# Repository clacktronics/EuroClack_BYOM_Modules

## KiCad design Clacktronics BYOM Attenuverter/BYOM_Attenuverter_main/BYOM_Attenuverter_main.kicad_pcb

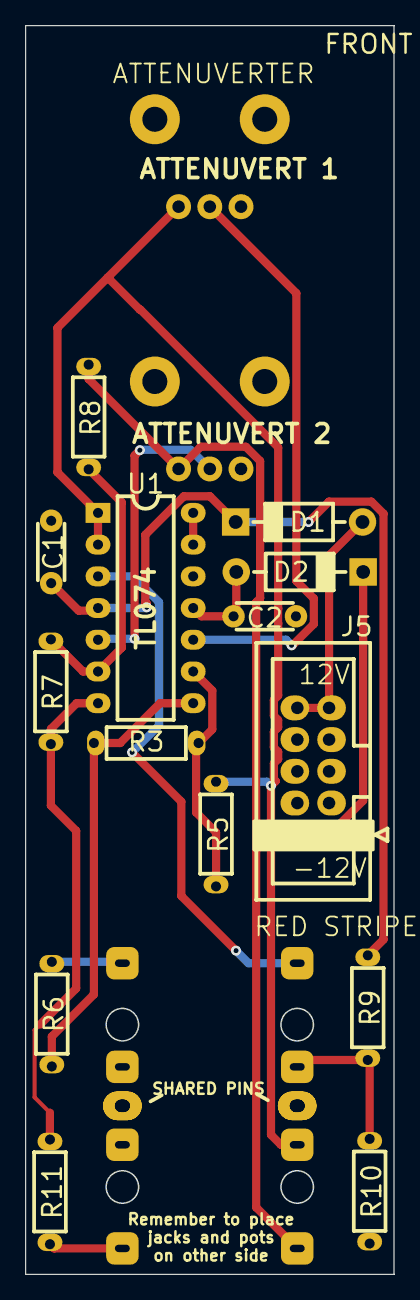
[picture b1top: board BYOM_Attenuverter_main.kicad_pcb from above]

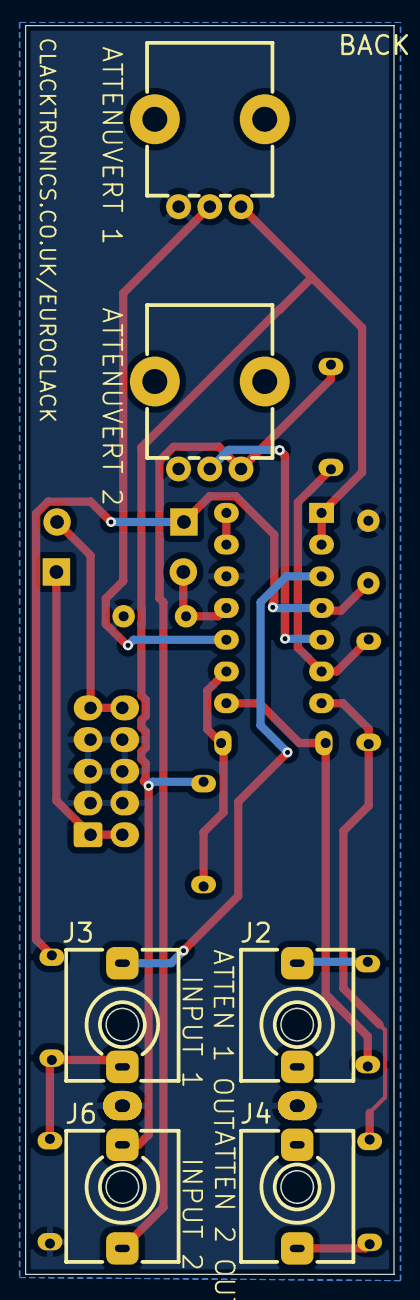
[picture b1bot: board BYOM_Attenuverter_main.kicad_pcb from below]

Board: 2 copper layers, 29.5 x 100.0 mm, 20 parts (6 on the bottom side), 18 nets.

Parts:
C1, C2: 100nF; C_TH_Disc_P5.00mm
D1, D2: 1N5817; D_TH_DO-41_P10.16mm
J2: Attenuvert 1; Jack_3.5mm_QingPu_WQP-PJ398SM_Vertical
J3: Input 1; Jack_3.5mm_QingPu_WQP-PJ398SM_Vertical
J4: Attenuvert 2; Jack_3.5mm_QingPu_WQP-PJ398SM_Vertical
J5: Eurorack socket; IDC-Header_2x05_P2.54mm_Vertical
J6: Input 2; Jack_3.5mm_QingPu_WQP-PJ398SM_Vertical
R3, R5, R7, R8, R9, R10: 100kΩ; R_Axial_DIN0204_L3.6mm_D1.6mm_P7.62mm_Horizontal
R6, R11: 1kΩ; R_Axial_DIN0204_L3.6mm_D1.6mm_P7.62mm_Horizontal
RV1, RV2: 100kΩ; POT_TH_Alps_RK09K_Single_Vertical
U1: TL074; DIP-14_W7.62mm_LongPads_copy

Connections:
+12V: C1.1, D1.1 (K), R9.1, U1.4 (V+)
-12V: C2.2, D2.2 (A), U1.11 (V-)
GND: C1.2, C2.1, J2.S, J3.S, J4.S, J5.3, J5.4, J5.5, J5.6, J5.7, J5.8, J6.S, R10.2, RV1.3, RV2.3, U1.12 (+)
unnamed: D1.2 (A), J5.9, J5.10
unnamed: D2.1 (K), J5.1, J5.2
unnamed: J2.T, R6.2
unnamed: J3.TN, R9.2, R10.1
unnamed: J4.T, R11.2
unnamed: J6.T, R8.1, RV2.1
unnamed: R3.2, R6.1, U1.8
unnamed: R7.2, R11.1, U1.7
unnamed: J3.T, U1.3 (+)
unnamed: J6.TN, R5.1, RV1.1, U1.1, U1.2 (-)
unnamed: RV2.2, U1.5 (+)
unnamed: R7.1, R8.2, U1.6 (-)
unnamed: RV1.2, U1.10 (+)
unnamed: R3.1, R5.2, U1.9 (-)
unnamed: U1.13 (-), U1.14

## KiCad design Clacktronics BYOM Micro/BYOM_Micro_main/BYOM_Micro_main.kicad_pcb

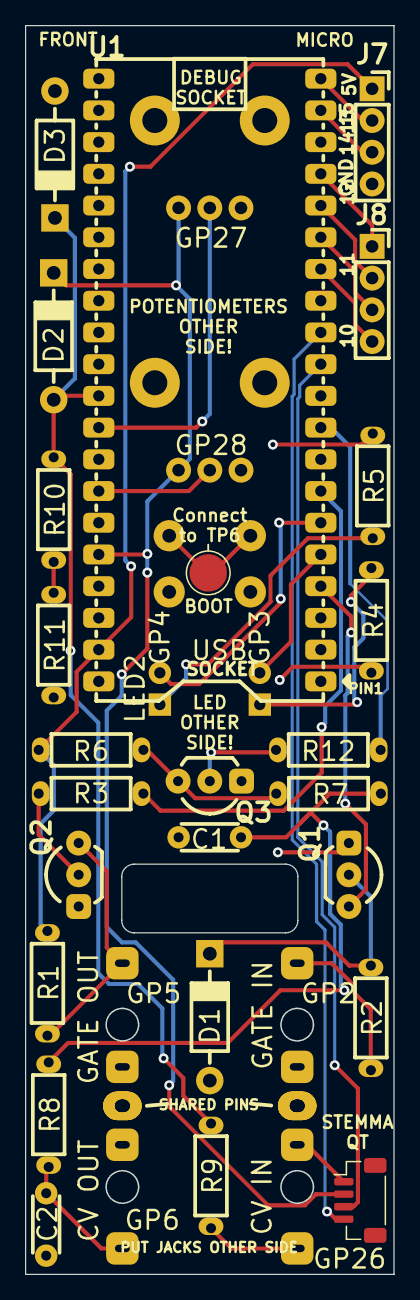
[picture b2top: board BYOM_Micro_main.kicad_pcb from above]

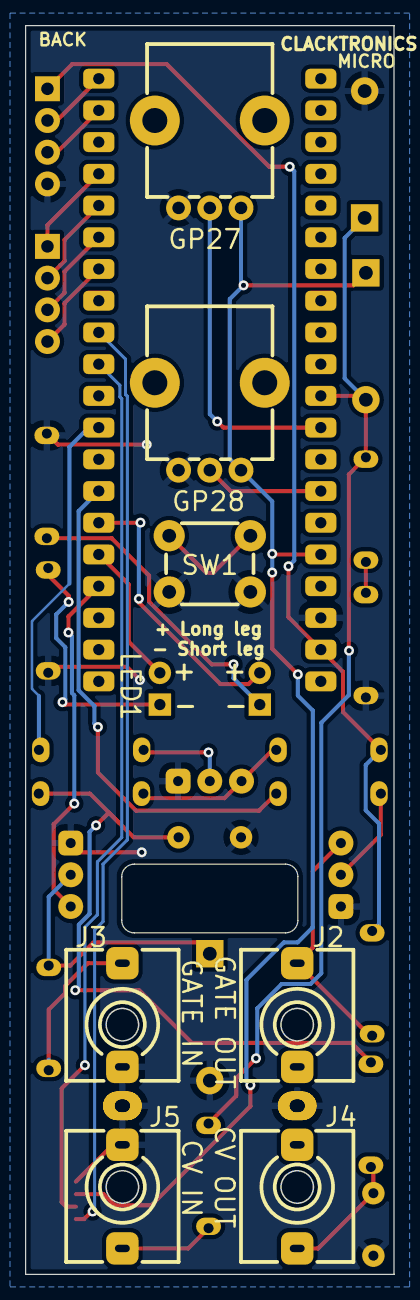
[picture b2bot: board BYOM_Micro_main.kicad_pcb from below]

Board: 2 copper layers, 29.5 x 100.0 mm, 34 parts (9 on the bottom side), 32 nets.

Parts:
C1: 100n; C_TH_Disc_P5.00mm
C2: 10n; C_TH_Disc_P5.00mm
D1, D2, D3: 1N5819WS; D_TH_DO-41_P10.16mm
J2: GATE_OUT; Jack_3.5mm_QingPu_WQP-PJ398SM_Vertical
J3: GATE_IN; Jack_3.5mm_QingPu_WQP-PJ398SM_Vertical
J4: CV_OUT; Jack_3.5mm_QingPu_WQP-PJ398SM_Vertical
J5: CV_IN; Jack_3.5mm_QingPu_WQP-PJ398SM_Vertical
J6: STEMMA QT; JST_SH_BM04B-SRSS-TB_1x04-1MP_P1.00mm_Vertical
J7: USB_HOST; PinSocket_1x04_P2.54mm_Vertical
J8: GPPINS; PinSocket_1x04_P2.54mm_Vertical
LED1, LED2: LED; LED_D3.0mm
Q1, Q2, Q3: 2N3904; TO-92_Inline_Wide
R1, R4, R5, R6, R8: 1k; R_Axial_DIN0204_L3.6mm_D1.6mm_P7.62mm_Horizontal
R2, R9, R10, R11: 100k; R_Axial_DIN0204_L3.6mm_D1.6mm_P7.62mm_Horizontal
R3, R12: 10k; R_Axial_DIN0204_L3.6mm_D1.6mm_P7.62mm_Horizontal
R7: 100R; R_Axial_DIN0204_L3.6mm_D1.6mm_P7.62mm_Horizontal
RV1, RV2: 100k; POT_TH_Alps_RK09K_Single_Vertical
SW1: Program; SW_PUSH_6mm
TP1: BOOT; TestPoint_Pad_D3.0mm
U1: Raspberry_Pi_Pico; RPI_Pico_through_hole

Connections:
+3.3V: D2.1 (K), J6.2, RV1.1, RV2.1, U1.36 (3V3(OUT))
+5V: J7.1, R1.1, R6.1, U1.39 (VSYS)
/I2C0_SCL: J6.4, U1.12 (GP9)
/I2C0_SDA: J6.3, U1.11 (GP8)
GND: C1.2, C2.2, D1.2 (A), D3.2 (A), J2.S, J3.S, J3.TN, J4.S, J5.S, J5.TN, J6.1, J7.4, Q1.1 (E), Q2.1 (E), Q3.1 (E), R4.2, R5.2, R11.1, RV1.3, RV2.3, SW1.2, U1.38 (GND)
unnamed: C1.1, R7.1, R8.2
unnamed: C2.1, J4.T, R8.1
unnamed: D1.1 (K), Q1.2 (B), R2.2
unnamed: D2.2 (A), D3.1 (K), R9.2, R10.2, U1.31 (GP26)
unnamed: J3.T, R2.1
unnamed: J5.T, R9.1
unnamed: J7.2, U1.20 (GP15)
unnamed: J7.3, U1.19 (GP14)
unnamed: J8.1, U1.17 (GP13)
unnamed: J8.2, U1.16 (GP12)
unnamed: J8.3, U1.15 (GP11)
unnamed: J8.4, U1.14 (GP10)
unnamed: LED1.2 (A), U1.5 (GP3)
unnamed: LED1.1 (K), R4.1
unnamed: LED2.2 (A), U1.6 (GP4)
unnamed: LED2.1 (K), R5.1
unnamed: Q1.3 (C), U1.4 (GP2)
unnamed: Q2.2 (B), R3.1
unnamed: J2.T, Q2.3 (C), R1.2
unnamed: Q3.2 (B), R12.1
unnamed: Q3.3 (C), R6.2, R7.2
unnamed: R10.1, R11.2
unnamed: SW1.1, TP1.1
unnamed: R3.2, U1.7 (GP5)
unnamed: R12.2, U1.9 (GP6)
unnamed: RV1.2, U1.32 (GP27)
unnamed: RV2.2, U1.34 (GP28)

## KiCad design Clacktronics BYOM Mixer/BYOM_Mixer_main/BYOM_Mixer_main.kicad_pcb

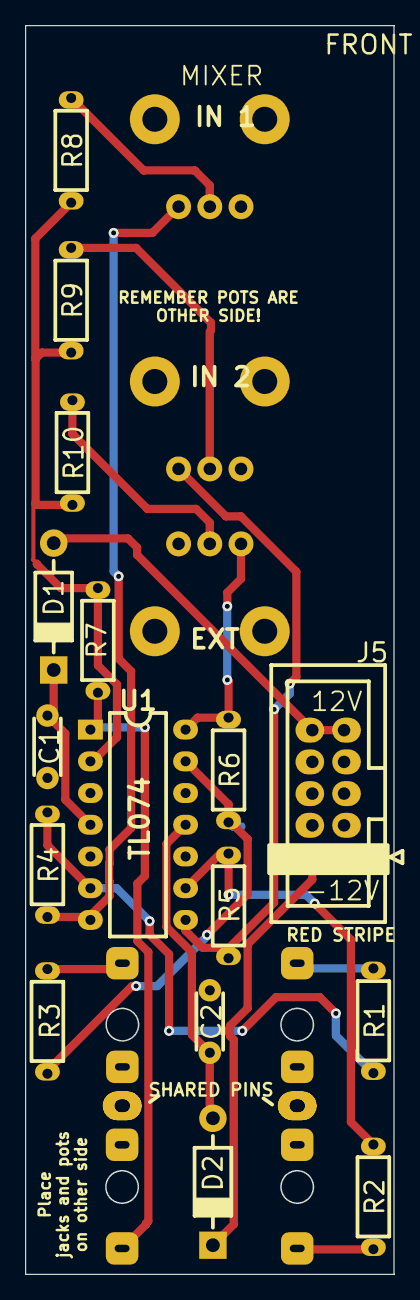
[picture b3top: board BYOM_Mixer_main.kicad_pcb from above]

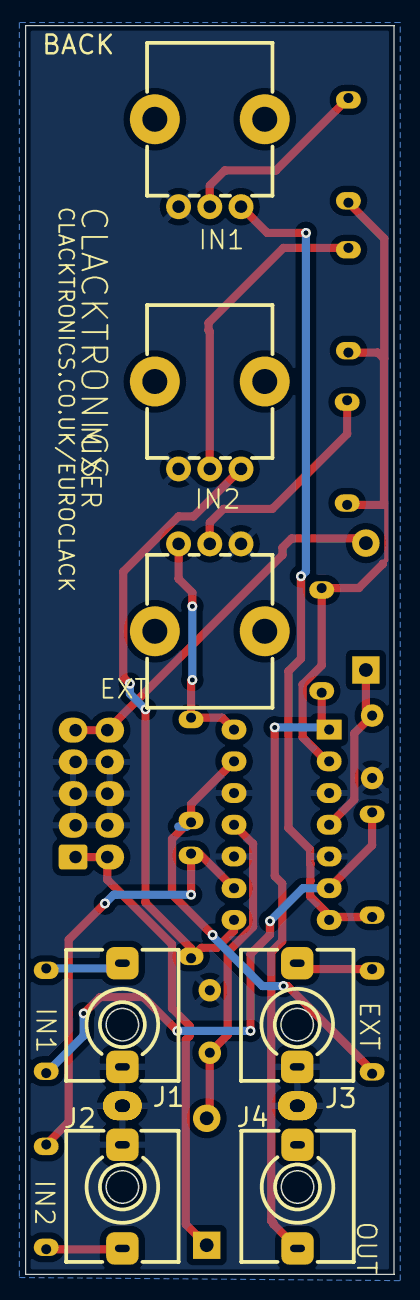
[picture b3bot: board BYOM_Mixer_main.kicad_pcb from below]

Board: 2 copper layers, 29.5 x 100.0 mm, 23 parts (7 on the bottom side), 19 nets.

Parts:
C1, C2: 100n; C_TH_Disc_P5.00mm
D1, D2: 1N5817; D_TH_DO-41_P10.16mm
J1: Input1; Jack_3.5mm_QingPu_WQP-PJ398SM_Vertical
J2: Input2; Jack_3.5mm_QingPu_WQP-PJ398SM_Vertical
J3: External; Jack_3.5mm_QingPu_WQP-PJ398SM_Vertical
J4: Output; Jack_3.5mm_QingPu_WQP-PJ398SM_Vertical
J5: Eurorack socket; IDC-Header_2x05_P2.54mm_Vertical
R1, R2, R3, R4, R5, R6, R7, R8, R9: 100kΩ; R_Axial_DIN0204_L3.6mm_D1.6mm_P7.62mm_Horizontal
R10: 1kΩ; R_Axial_DIN0204_L3.6mm_D1.6mm_P7.62mm_Horizontal
RV1, RV2, RV3: 100kΩ; POT_TH_Alps_RK09K_Single_Vertical
U1: TL074; DIP-14_W7.62mm_LongPads_copy

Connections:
+12V: C1.1, D1.1 (K), U1.4 (V+)
-12V: C2.2, D2.2 (A), U1.11 (V-)
GND: C1.2, C2.1, J1.S, J1.TN, J2.S, J2.TN, J3.S, J3.TN, J4.S, J5.3, J5.4, J5.5, J5.6, J5.7, J5.8, RV1.3, RV2.3, RV3.3, U1.3 (+), U1.5 (+), U1.10 (+), U1.12 (+)
unnamed: D1.2 (A), J5.9, J5.10
unnamed: D2.1 (K), J5.1, J5.2
unnamed: J1.T, R1.1
unnamed: J2.T, R2.1
unnamed: J3.T, R3.1
unnamed: J4.T, R7.2, U1.1
unnamed: R4.2, RV1.1, U1.7
unnamed: R5.2, RV2.1, U1.8
unnamed: R6.2, RV3.1, U1.14
unnamed: R8.1, RV1.2
unnamed: R9.1, RV2.2
unnamed: R10.1, RV3.2
unnamed: R7.1, R8.2, R9.2, R10.2, U1.2 (-)
unnamed: R1.2, R4.1, U1.6 (-)
unnamed: R2.2, R5.1, U1.9 (-)
unnamed: R3.2, R6.1, U1.13 (-)

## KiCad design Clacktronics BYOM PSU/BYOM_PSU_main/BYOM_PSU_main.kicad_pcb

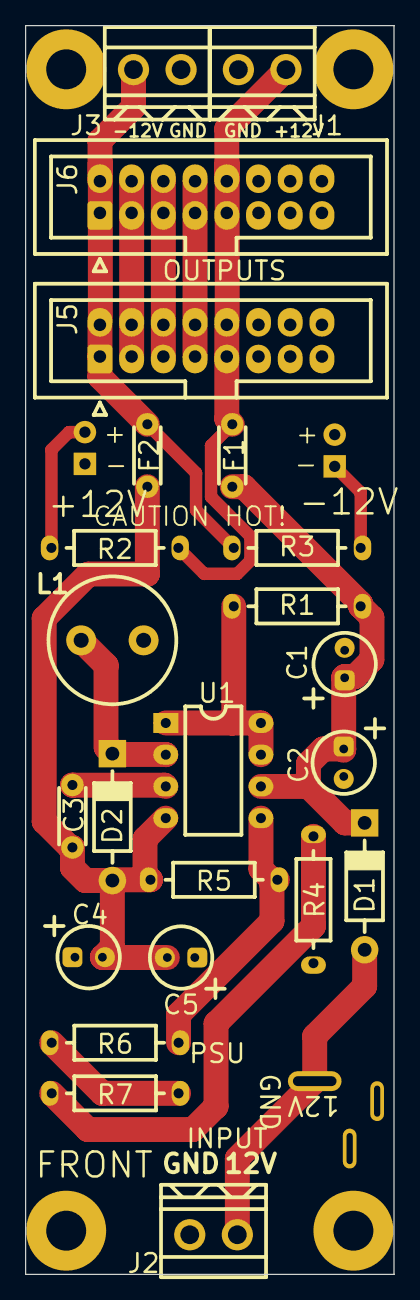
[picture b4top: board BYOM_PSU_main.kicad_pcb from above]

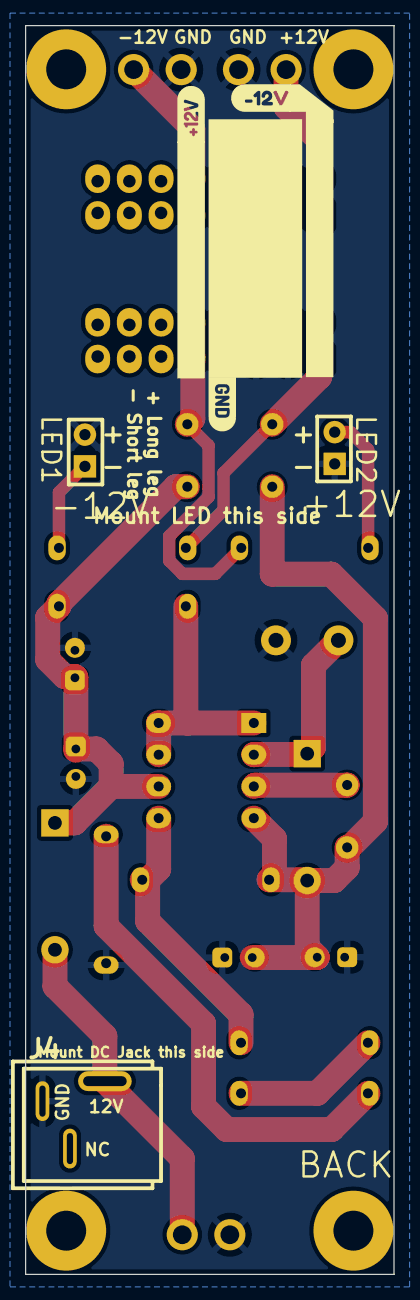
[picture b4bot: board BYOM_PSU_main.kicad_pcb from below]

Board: 2 copper layers, 29.5 x 100.0 mm, 29 parts (6 on the bottom side), 14 nets.

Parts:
C1, C2, C4, C5: 100μF; C_TH_Elec_5mm_P2mm
C3: 220pF; C_TH_Disc_P5.00mm
D1, D2: 1N5817; D_TH_DO-41_P10.16mm
F1, F2: JK60-030; C_TH_Disc_P5.00mm
J1: +12V; 5.08 01X02
J2: 12V Input Screw terminal; 5.08 01X02
J3: -12V; 5.08 01X02
J4: 12V input; DC-IN-TH_DC-012A-20A
J5, J6: EURORACK_16_PIN; IDC-Header_2x08_P2.54mm_Vertical
L1: 220μH; L_Radial_D10.0mm_P5.00mm_Neosid_SD12_style3
LED1, LED2: LED; LED_D3.0mm
R1: 1Ω; R_TH_Axial_250mw_P10.16mm_Horizontal
R2, R3, R5, R6, R7: 1.5kΩ; R_TH_Axial_250mw_P10.16mm_Horizontal
R4: 10kΩ; R_TH_Axial_250mw_P10.16mm_Horizontal
U1: MC34063AD; DIP-8_W7.62mm_LongPads
kibuzzard-63C1369E: G***; kibuzzard-63C1369E
kibuzzard-63C13629: G***; kibuzzard-63C13629
kibuzzard-6399AAFB: G***; kibuzzard-6399AAFB

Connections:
+12V: F1.2, J1.2, J5.9, J5.10, J6.9, J6.10, R2.2
-12V: F2.2, J3.1, J5.1, J5.2, J6.1, J6.2, R3.2
GND: C1.2, C2.2, C4.1, C5.1, J1.1, J2.2, J3.2, J4.2, J5.3, J5.4, J5.5, J5.6, J5.7, J5.8, J6.3, J6.4, J6.5, J6.6, J6.7, J6.8, L1.2, LED1.2 (A), LED2.1 (K), R4.1
unnamed: D1.2 (A), J2.1, J4.1
unnamed: C3.2, C4.2, C5.2, D2.2 (A), F2.1, R5.1, U1.4 (GND)
unnamed: D2.1 (K), L1.1, U1.2 (SwE)
unnamed: LED1.1 (K), R3.1
unnamed: LED2.2 (A), R2.1
unnamed: R4.2, R7.1
unnamed: R6.1, R7.2
unnamed: R1.2, U1.1 (SwC), U1.7 (Ipk), U1.8 (DC)
unnamed: C3.1, U1.3 (TC)
unnamed: R5.2, R6.2, U1.5 (Vfb)
VCC: C1.1, C2.1, D1.1 (K), F1.1, R1.1, U1.6 (Vin)

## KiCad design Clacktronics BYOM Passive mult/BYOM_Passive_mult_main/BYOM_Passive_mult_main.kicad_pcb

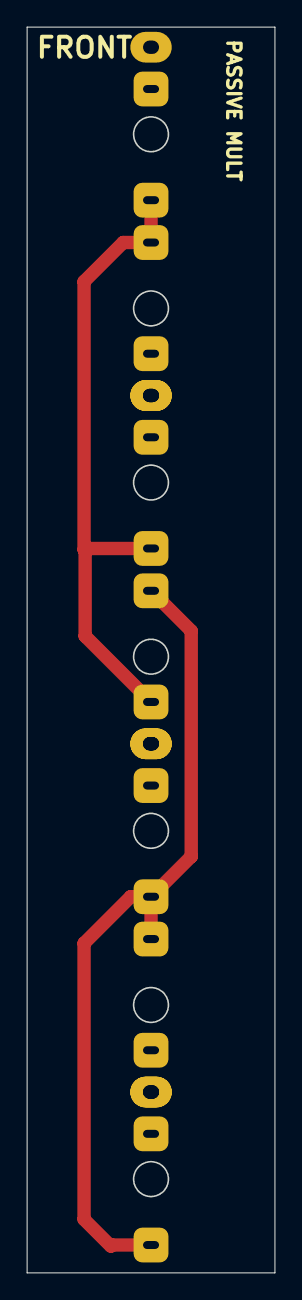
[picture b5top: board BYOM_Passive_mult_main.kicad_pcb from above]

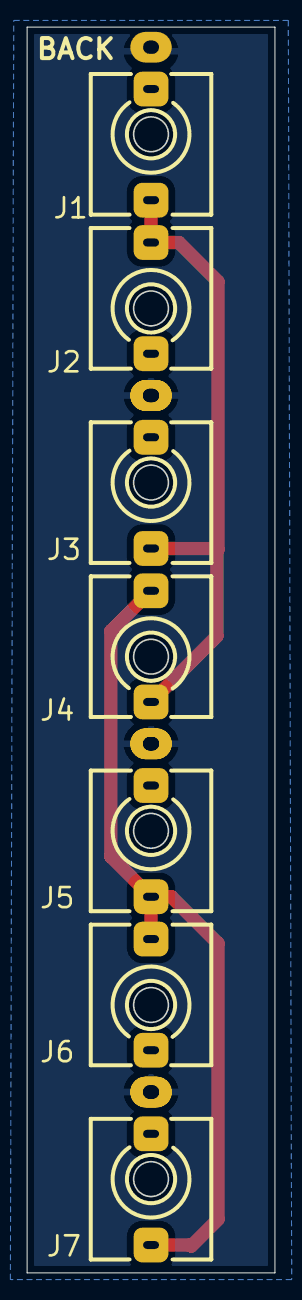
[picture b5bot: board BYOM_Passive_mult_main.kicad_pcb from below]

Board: 2 copper layers, 18.5 x 93.0 mm, 7 parts (7 on the bottom side), 3 nets.

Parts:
J1, J2, J3, J4, J5, J6, J7: AudioJack2_SwitchT; Jack_3.5mm_QingPu_WQP-PJ398SM_Vertical

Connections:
GND: J1.S, J2.S, J3.S, J4.S, J5.S, J6.S, J7.S
unnamed: J1.T, J2.T, J3.T, J4.TN
unnamed: J4.T, J5.T, J6.T, J7.T
